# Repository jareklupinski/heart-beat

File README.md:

# heart-beat
A redesigned 808-synth clone

After hearing Ke$ha ask "do i make your heart beat like an 808 drum", I realized that I had no idea what an 808 drum sounded like. The parts to build a clone aren't that expensive.

This design was built, tested, and is working. It had an issue with the Accent ability that needs attention.

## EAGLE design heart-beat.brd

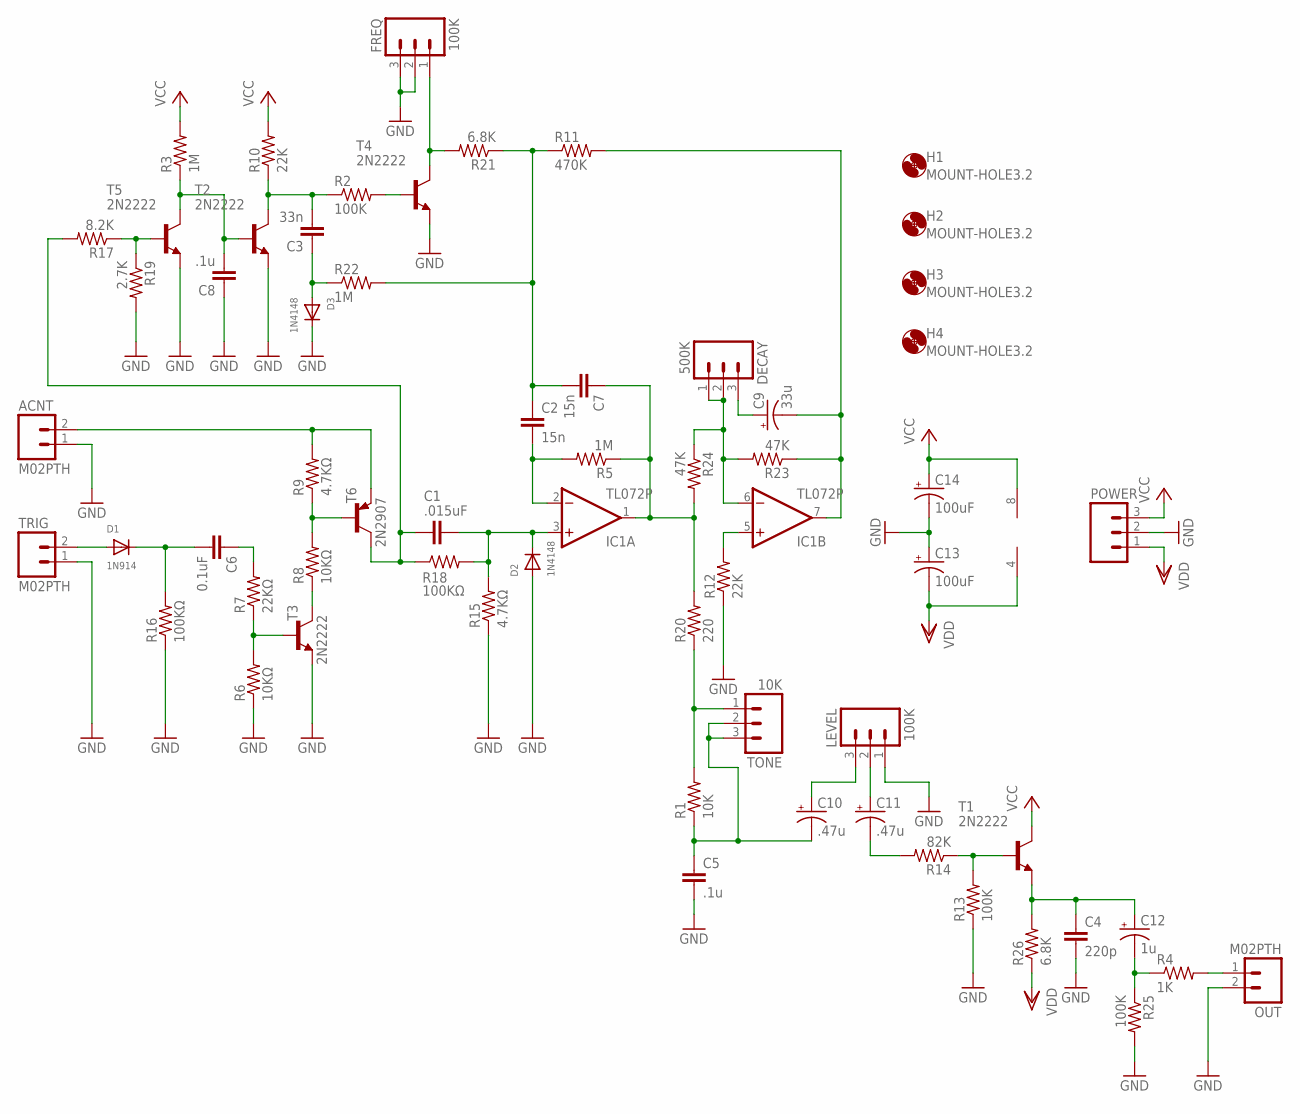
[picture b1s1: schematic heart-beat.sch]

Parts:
ACNT: M02PTH; 1X02
C1: .015uF; C025-024X044
C2, C7: 15n; C025-024X044
C3: 33n; C025-024X044
C4: 220p; C025-024X044
C5, C8: .1u; C025-024X044
C6: 0.1uF; C025-024X044
C9: 33u; E2,5-6E
C10, C11: .47u; E2,5-6E
C12: 1u; E2,5-6E
C13, C14: 100uF; E2,5-6E
D1: 1N914; 1N4148
D2, D3: 1N4148
DECAY: 500K; 1X03
FREQ: 100K; 1X03
H1, H2, H3, H4: MOUNT-HOLE3.2; 3,2
IC1: TL072P; DIL08
LEVEL: 100K; 1X03
OUT: M02PTH; 1X02
POWER: M03PTH; 1X03
R1: 10K; 0204/5
R2, R13, R25: 100K; 0204/5
R3, R5, R22: 1M; 0204/5
R4: 1K; 0204/5
R6, R8: 10KΩ; 0204/5
R7: 22KΩ; 0204/5
R9, R15: 4.7KΩ; 0204/5
R10, R12: 22K; 0204/5
R11: 470K; 0204/5
R14: 82K; 0204/5
R16, R18: 100KΩ; 0204/5
R17: 8.2K; 0204/5
R19: 2.7K; 0204/5
R20: 220; 0204/5
R21, R26: 6.8K; 0204/5
R23, R24: 47K; 0204/5
T1, T2, T3, T4, T5: 2N2222; TO92-EBC-OVAL
T6: 2N2907; TO92-EBC-OVAL
TONE: 10K; 1X03
TRIG: M02PTH; 1X02

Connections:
ACCNT: ACNT.2, R9.2, T6.E
GND: ACNT.1, C4.2, C5.2, C8.1, C13.+, C14.-, D2.A, D3.K (C), FREQ.2, FREQ.3, LEVEL.1, OUT.2, POWER.2, R6.1, R12.1, R13.1, R15.1, R16.1, R19.2, R25.2, T2.E, T3.E, T4.E, T5.E, TRIG.1
unnamed: R17.1, R19.1, T5.B
unnamed: C9.+, DECAY.3
unnamed: R13.2, R14.1, T1.B
unnamed: R8.2, R9.1, T6.B
unnamed: C3.1, D3.A, R22.1
unnamed: C2.1, C7.2, R11.1, R21.1, R22.2
unnamed: D1.A, TRIG.2
unnamed: C12.-, R4.1, R25.1
unnamed: C11.-, R14.2
unnamed: R8.1, T3.C
unnamed: C4.1, C12.+, R26.2, T1.E
unnamed: R2.2, T4.B
unnamed: C11.+, LEVEL.2
unnamed: C10.+, LEVEL.3
unnamed: C3.2, R2.1, R10.1, T2.C
unnamed: C8.2, R3.1, T2.B, T5.C
unnamed: FREQ.1, R21.2, T4.C
unnamed: C6.2, D1.K (C), R16.2
unnamed: R6.2, R7.1, T3.B
unnamed: IC1.5 (+IN), R12.2
unnamed: R1.2, R20.1, TONE.1
unnamed: OUT.1, R4.2
unnamed: C2.2, IC1.2 (-IN), R5.2
unnamed: C5.1, C10.-, R1.1, TONE.2, TONE.3
unnamed: C9.-, IC1.7 (OUT), R11.2, R23.1
unnamed: C1.2, R17.2, R18.1, T6.C
unnamed: C1.1, D2.K (C), IC1.3 (+IN), R15.2, R18.2
unnamed: C7.1, IC1.1 (OUT), R5.1, R20.2, R24.2
unnamed: DECAY.1, DECAY.2, IC1.6 (-IN), R23.2, R24.1
unnamed: C6.1, R7.2
VCC: C14.+, IC1.8 (V+), POWER.3, R3.2, R10.2, T1.C
VDD: C13.-, IC1.4 (V-), POWER.1, R26.1

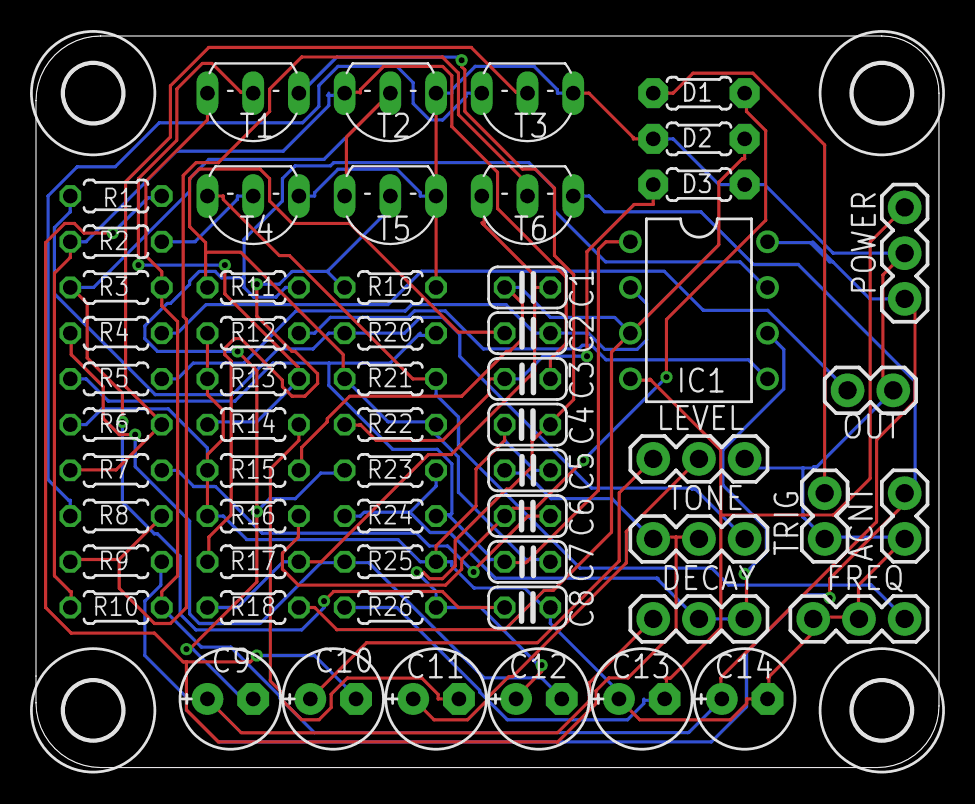
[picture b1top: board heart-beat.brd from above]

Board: 2 copper layers, 50.2 x 40.6 mm, 62 parts (0 on the bottom side), 34 nets.

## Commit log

2018-07-04 prototype tested- working
2018-07-04 added pictures of board and schematic

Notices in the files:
parts and their libraries:
SparkFun-Connectors: Licensing: CC v3.0 Share-Alike You are welcome to use this library for commercial purposes.
